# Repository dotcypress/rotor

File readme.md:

# rotor

STSPIN220/STSPIN250 breakout board.

## License

Licensed under either of

- Apache License, Version 2.0 ([LICENSE-APACHE](LICENSE-APACHE) or
  http://www.apache.org/licenses/LICENSE-2.0)
- MIT license ([LICENSE-MIT](LICENSE-MIT) or http://opensource.org/licenses/MIT)

at your option.

### Contribution

Unless you explicitly state otherwise, any contribution intentionally submitted
for inclusion in the work by you, as defined in the Apache-2.0 license, shall be
dual licensed as above, without any additional terms or conditions.

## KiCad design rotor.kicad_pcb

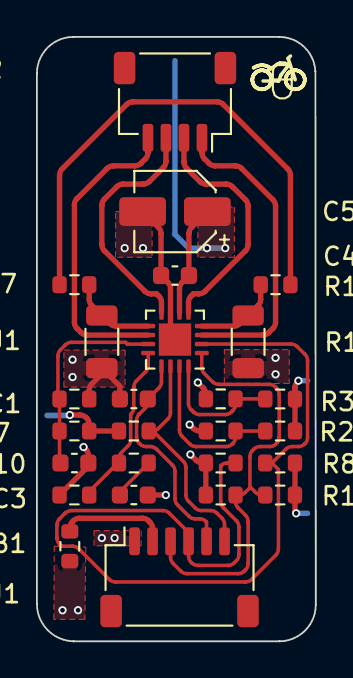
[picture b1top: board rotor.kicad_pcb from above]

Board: 2 copper layers, 15.5 x 33.6 mm, 26 parts (0 on the bottom side), 19 nets.

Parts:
C1, C2: 1uF; C_0603_1608Metric
C3: 12nF; C_0603_1608Metric
C4: 10uF; C_0603_1608Metric
C5: 22uF; CP_Elec_4x4.5
FB1: FerriteBead; R_0603_1608Metric
J1: INPUT; JST_SH_SM06B-SRSS-TB_1x06-1MP_P1.00mm_Horizontal
J2: Motor; JST_SH_SM04B-SRSS-TB_1x04-1MP_P1.00mm_Horizontal
R1, R2, R3, R6, R8, R9, R11, R13, R16, R17: DNP; R_0603_1608Metric
R4, R5: Rref; R_0603_1608Metric
R7: 10KΩ; R_0603_1608Metric
R10: 1KΩ; R_0603_1608Metric
R12: 47KΩ; R_0603_1608Metric
R14, R15: Rsense; R_1206_3216Metric
U1: STSPIN220/STSPIN250; VQFN-16-1EP_3x3mm_P0.5mm_EP1.8x1.8mm

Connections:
GND: C1.2, C2.2, C3.2, C4.2, C5.2, J1.1, R2.1, R3.1, R5.2, R8.1, R11.1, R12.2, R14.1, R15.1, U1.7 (GND), U1.17 (EPAD)
unnamed: C3.1, R10.2
unnamed: FB1.1, J1.2
unnamed: J1.3, R11.2, R13.1, U1.1 (DIR)
unnamed: J1.4, R8.2, R9.1, U1.2 (STCK)
unnamed: C1.1, J1.5, U1.13 (EN/FLT)
unnamed: J1.6, R7.2, U1.14 (STBY/RESET)
unnamed: J2.1, U1.3 (OUTA1)
unnamed: J2.2, U1.5 (OUTA2)
unnamed: J2.3, U1.8 (OUTB2)
unnamed: J2.4, U1.10 (OUTB1)
unnamed: R16.2, R17.1
unnamed: R3.2, R6.1, U1.16 (MODE1)
unnamed: R1.1, R2.2, U1.15 (MODE2)
unnamed: C2.1, R4.1, R5.1, U1.11 (REF)
unnamed: R14.2, R16.1, U1.4 (SENSEA)
unnamed: R15.2, R17.2, U1.9 (SENSEB)
unnamed: R10.1, R12.1, U1.12 (TOFF)
VDD: C4.1, C5.1, FB1.2, R1.2, R4.2, R6.2, R7.1, R9.2, R13.2, U1.6 (VS)

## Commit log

2022-07-19 rev 0.1
2022-07-21 add readme
